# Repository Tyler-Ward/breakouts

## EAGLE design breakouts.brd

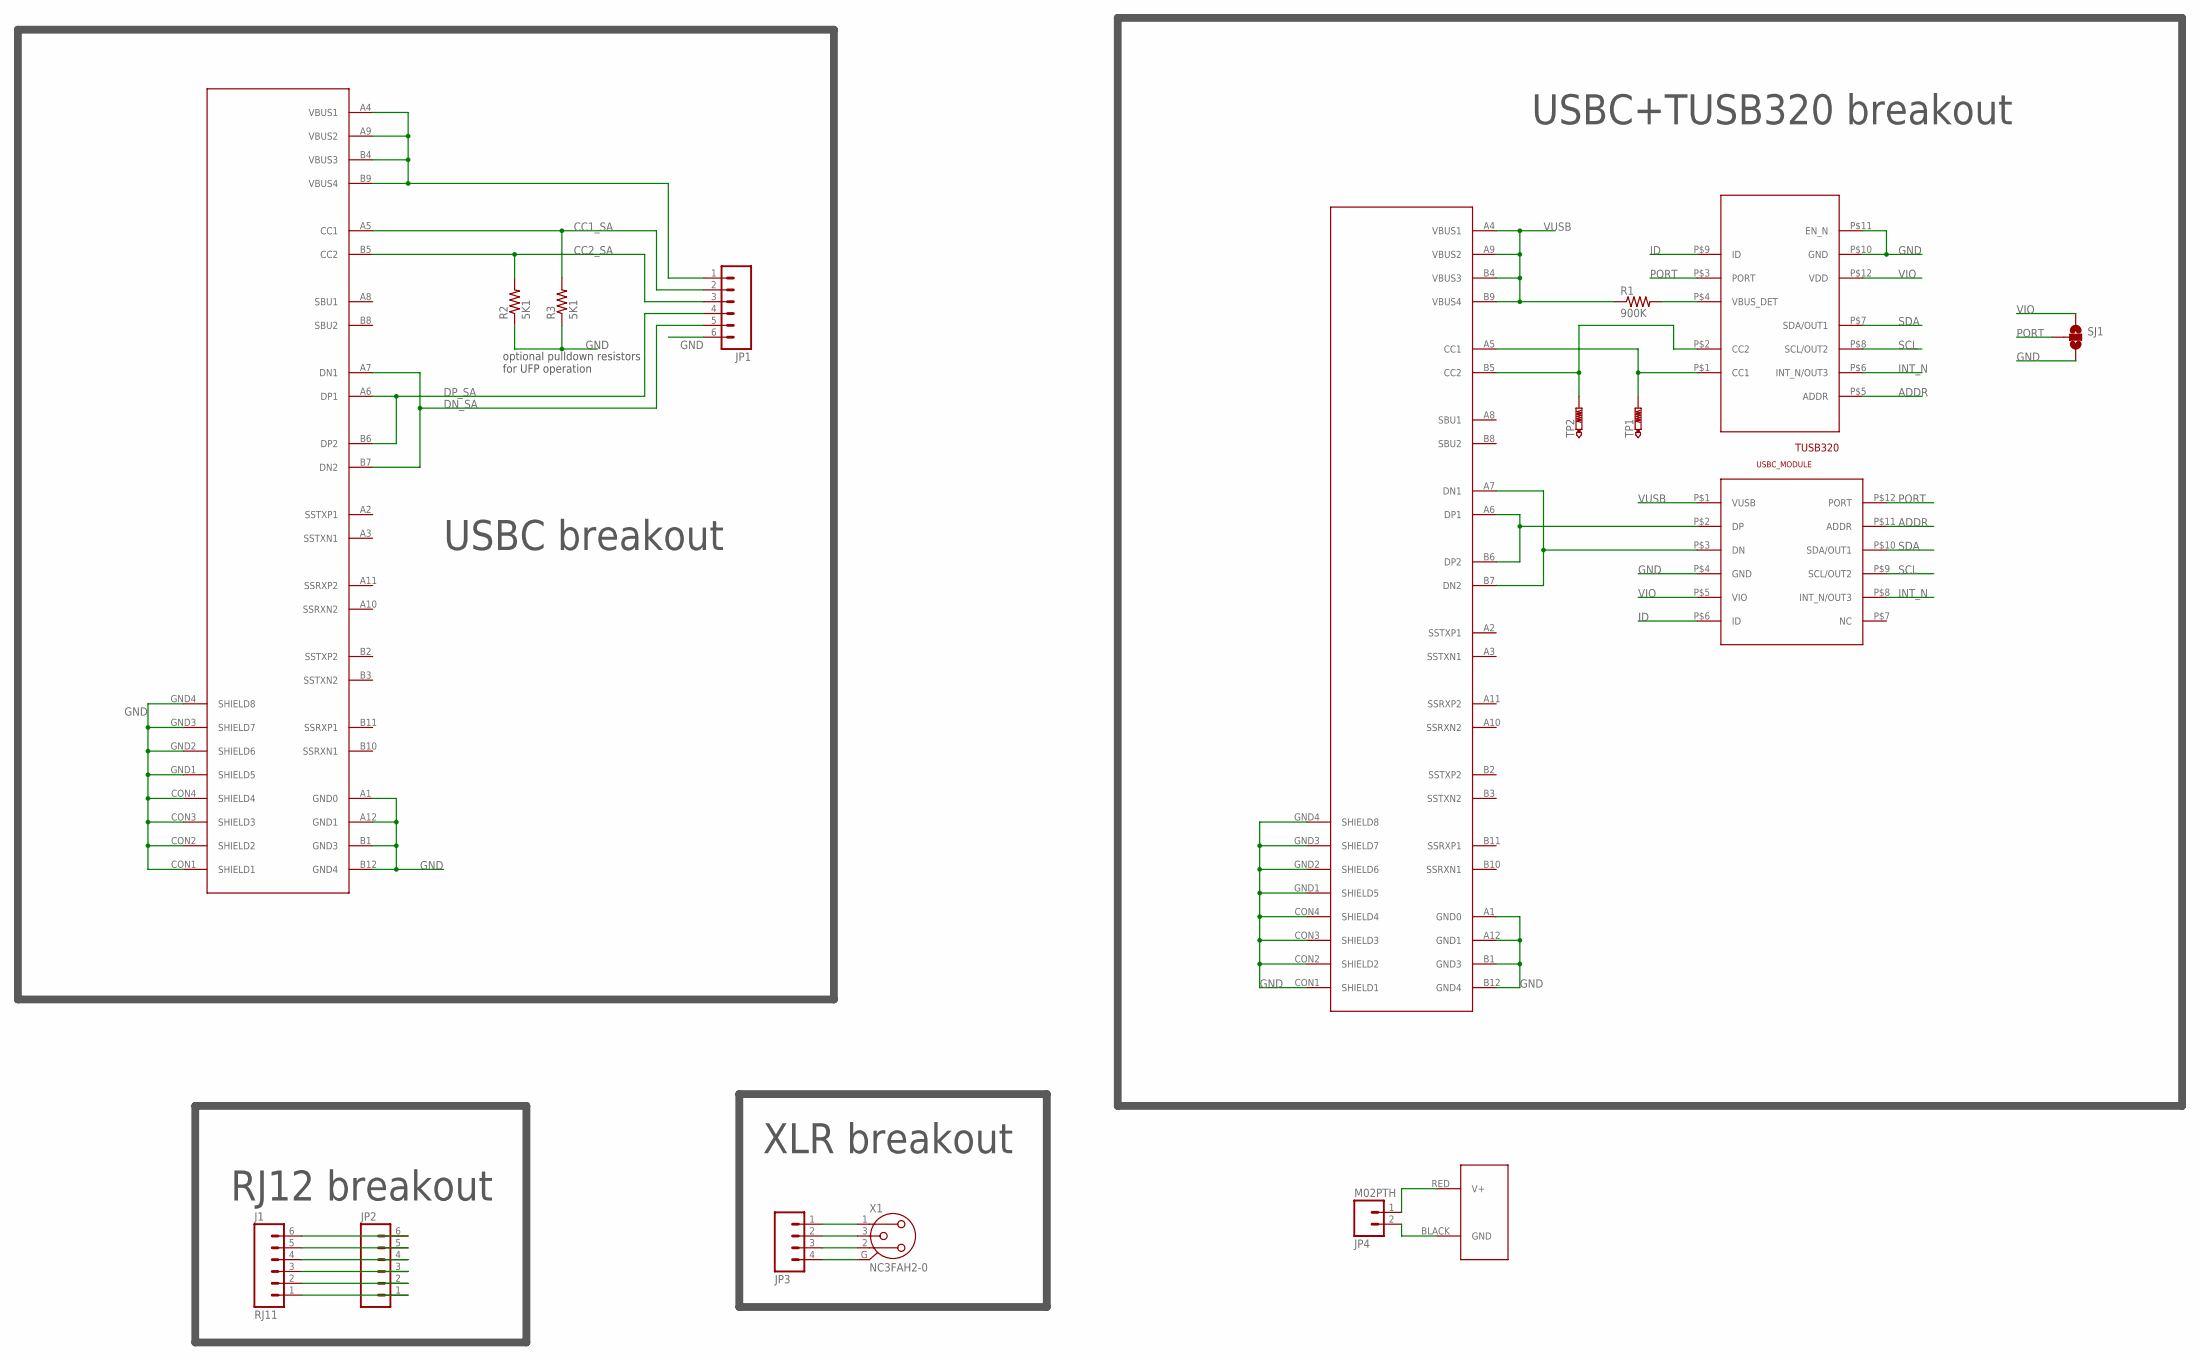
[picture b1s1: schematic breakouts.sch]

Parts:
CONN1, CONN2: USB-C_WURTH_632723X00011USB-C; USB-C_WURTH_632723X00011
J1: RJ11; RJ11-6
J2: POWERPOLE_POWER25A; POWERPOLE_PAIR_25A
JP1, JP2: M06SIP; 1X06
JP3: M04PTH; 1X04
JP4: M02PTH; 1X02
R1: 900K; 0603-RES
R2, R3: 5K1; 0603-RES
SJ1: SOLDERJUMPER_2WAYS; SJ_3
TP1, TP2: PTR1TP10R; TP10R
U$1: TUSB320XQFN; X2QFN
U$2: USBC_BREAKOUTPDIP; DIP12_6WIDE
X1: NC3FAH2-0

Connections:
ADDR: U$1.P$5 (ADDR), U$2.P$11 (ADDR)
CC1: CONN1.A5 (CC1), TP1.TP, U$1.P$1 (CC1)
CC1_SA: CONN2.A5 (CC1), JP1.2, R3.2
CC2: CONN1.B5 (CC2), TP2.TP, U$1.P$2 (CC2)
CC2_SA: CONN2.B5 (CC2), JP1.3, R2.2
DN: CONN1.A7 (DN1), CONN1.B7 (DN2), U$2.P$3 (DN)
DN_SA: CONN2.A7 (DN1), CONN2.B7 (DN2), JP1.5
DP: CONN1.A6 (DP1), CONN1.B6 (DP2), U$2.P$2 (DP)
DP_SA: CONN2.A6 (DP1), CONN2.B6 (DP2), JP1.4
GND: CONN1.A1 (GND0), CONN1.A12 (GND1), CONN1.B1 (GND3), CONN1.B12 (GND4), CONN1.CON1 (SHIELD1), CONN1.CON2 (SHIELD2), CONN1.CON3 (SHIELD3), CONN1.CON4 (SHIELD4), CONN1.GND1 (SHIELD5), CONN1.GND2 (SHIELD6), CONN1.GND3 (SHIELD7), CONN1.GND4 (SHIELD8), CONN2.A1 (GND0), CONN2.A12 (GND1), CONN2.B1 (GND3), CONN2.B12 (GND4), CONN2.CON1 (SHIELD1), CONN2.CON2 (SHIELD2), CONN2.CON3 (SHIELD3), CONN2.CON4 (SHIELD4), CONN2.GND1 (SHIELD5), CONN2.GND2 (SHIELD6), CONN2.GND3 (SHIELD7), CONN2.GND4 (SHIELD8), JP1.6, R2.1, R3.1, SJ1.3, U$1.P$10 (GND), U$1.P$11 (EN_N), U$2.P$4 (GND)
ID: U$1.P$9 (ID), U$2.P$6 (ID)
INT_N: U$1.P$6 (INT_N/OUT3), U$2.P$8 (INT_N/OUT3)
unnamed: J1.1, JP2.1
unnamed: J1.2, JP2.2
unnamed: J1.3, JP2.3
unnamed: J1.4, JP2.4
unnamed: J1.5, JP2.5
unnamed: J1.6, JP2.6
unnamed: JP3.1, X1.1
unnamed: JP3.2, X1.3
unnamed: R1.2, U$1.P$4 (VBUS_DET)
unnamed: JP3.3, X1.2
unnamed: JP3.4, X1.G
unnamed: J2.RED (V+), JP4.1
unnamed: J2.BLACK (GND), JP4.2
PORT: SJ1.2, U$1.P$3 (PORT), U$2.P$12 (PORT)
SCL: U$1.P$8 (SCL/OUT2), U$2.P$9 (SCL/OUT2)
SDA: U$1.P$7 (SDA/OUT1), U$2.P$10 (SDA/OUT1)
VBUS_SA: CONN2.A4 (VBUS1), CONN2.A9 (VBUS2), CONN2.B4 (VBUS3), CONN2.B9 (VBUS4), JP1.1
VIO: SJ1.1, U$1.P$12 (VDD), U$2.P$5 (VIO)
VUSB: CONN1.A4 (VBUS1), CONN1.A9 (VBUS2), CONN1.B4 (VBUS3), CONN1.B9 (VBUS4), R1.1, U$2.P$1 (VUSB)

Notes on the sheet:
USBC+TUSB320 breakout
optional pulldown resistors for UFP operation
USBC breakout
RJ12 breakout
XLR breakout

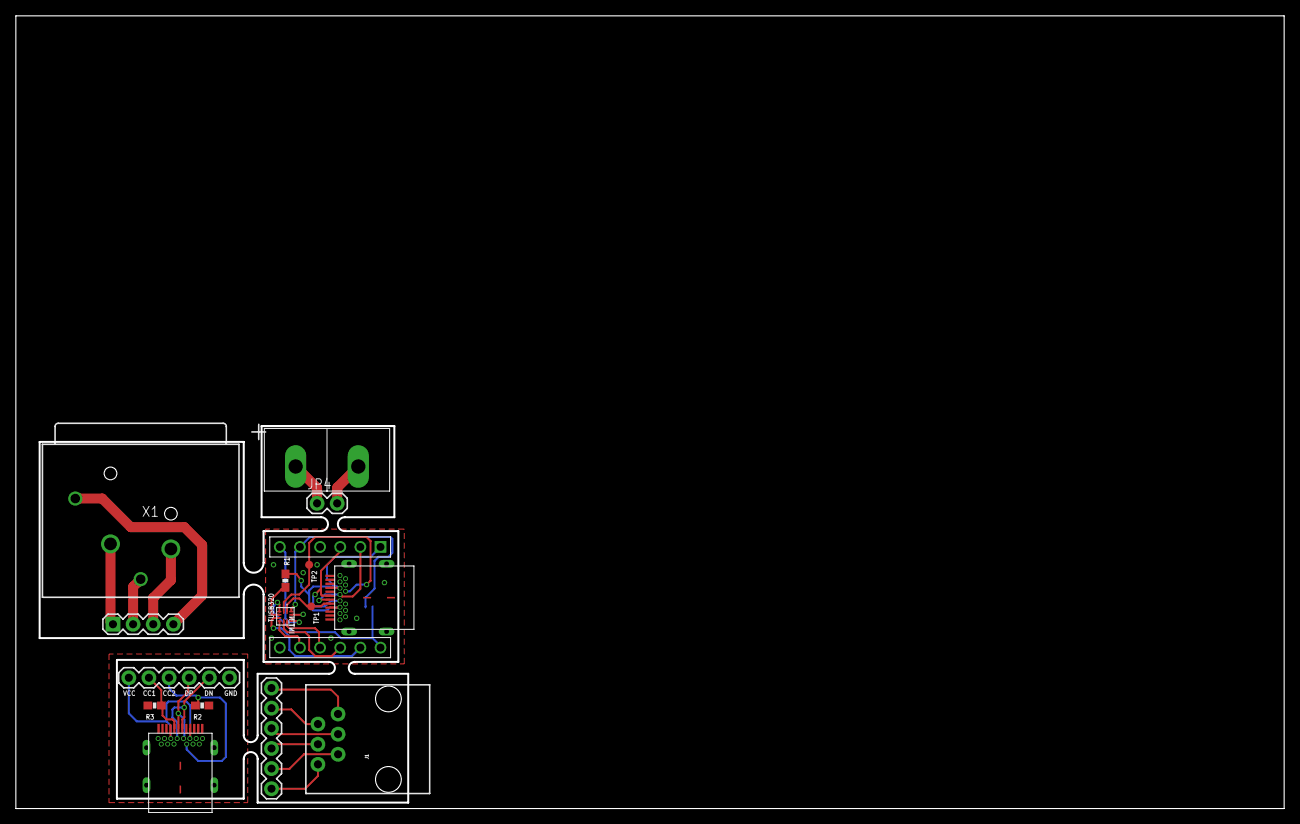
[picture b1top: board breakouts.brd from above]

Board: 2 copper layers, 160.0 x 100.0 mm, 17 parts (1 on the bottom side), 31 nets.

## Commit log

2016-02-11 Added initial breakout board of set consisting of a USBC+TUSB breakout
2016-02-12 Added USB C breakout with CC pulldown resistors
2016-02-12 Added RJ12 breakout
2016-02-13 Panalised breakouts and added powerpole breakout
2016-02-14 minor changes for gerber generation
2016-02-14 Added readme and gitignore

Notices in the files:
parts and their libraries:
SparkFun-Passives: Licensing: Creative Commons ShareAlike 4.0 International - https://creativecommons.org/licenses/by-sa/4.0
SparkFun: Licensing: CC v3.0 Share-Alike You are welcome to use this library for commercial purposes.
